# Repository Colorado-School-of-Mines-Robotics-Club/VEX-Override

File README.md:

# VEX Override

This is the codebase for VURC team ORDGR's 26-27 Override season.

## Development environment setup

A nix flake is provided with a `devShell` output providing all the necessary
tools plus some extra. If you have nix installed, you can use that. If you
don't, all the necessary tools are listed below:

1. `rustup`
    - Follow the instructions at https://www.rust-lang.org/tools/install
    - This project requires nightly and has a `rust-toolchain.toml` defining the specific toolchain version.
2. `cargo-v5`
    - Used for building and uploading to the brain
    - Can be installed with cargo: `cargo install cargo-v5`
3. `picotool`
    - Used for uploading code to the Pico microcontroller over BOOTSEL mode
    - If using a probe tool, this isn't strictly necessary
    - Can be downloaded from the official Pico SDK at `https://github.com/raspberrypi/pico-sdk-tools/releases`
    - Example: `picotool load -u -v -x -t elf <executable>`
4. `probe-rs`
    - Used for uploading code and debugging the Pico microcontroller with a probe tool
    - If no probe tool is available, use BOOTSEL mode and `picotool` instead
    - Can be installed with cargo: `cargo install probe-rs`

## Project layout

> [!IMPORTANT]
> Due to limitations in how cargo handles multi-target projects, you
> must actively be in the `brain/` or `pico/` folder to build or upload
> code: run `cd brain` or `cd pico` before using any cargo commands.

| Folder                                     | Description                                                                                                                   |
| ------------------------------------------ | ----------------------------------------------------------------------------------------------------------------------------- |
| [`brain/bots`](./brain/bots)               | Top-level code running on our bots' v5 brains, setting up subsystems and declaring autonomous routes                          |
| [`brain/common`](./brain/common)           | Bot-agnostic v5 brain code such as shared subsystems or display logic                                                         |
| [`brain/coprocessor`](./brain/coprocessor) | Brain-side logic for communicating with the Pico microcontroller                                                              |
| [`pico/`](./pico/)                         | The code running on the Raspberry Pi Pico 2 microcontroller we use on our bots                                                |
| [`rplidar/`](./rplidar)                    | Rust code implementing the prococol for RPLIDAR S & C series devices, may be factored out into a seperate crate at some point |
| [`swerve_c++/`](./swerve_c++)              | Prototype C++ (PROS) code used for initially testing the swerve bot                                                           |
| [`pcb/`](./pcb)                            | The kicad files (schematics, layouts, etc) for the custom PCB connected to our Picos and v5 brains                            |

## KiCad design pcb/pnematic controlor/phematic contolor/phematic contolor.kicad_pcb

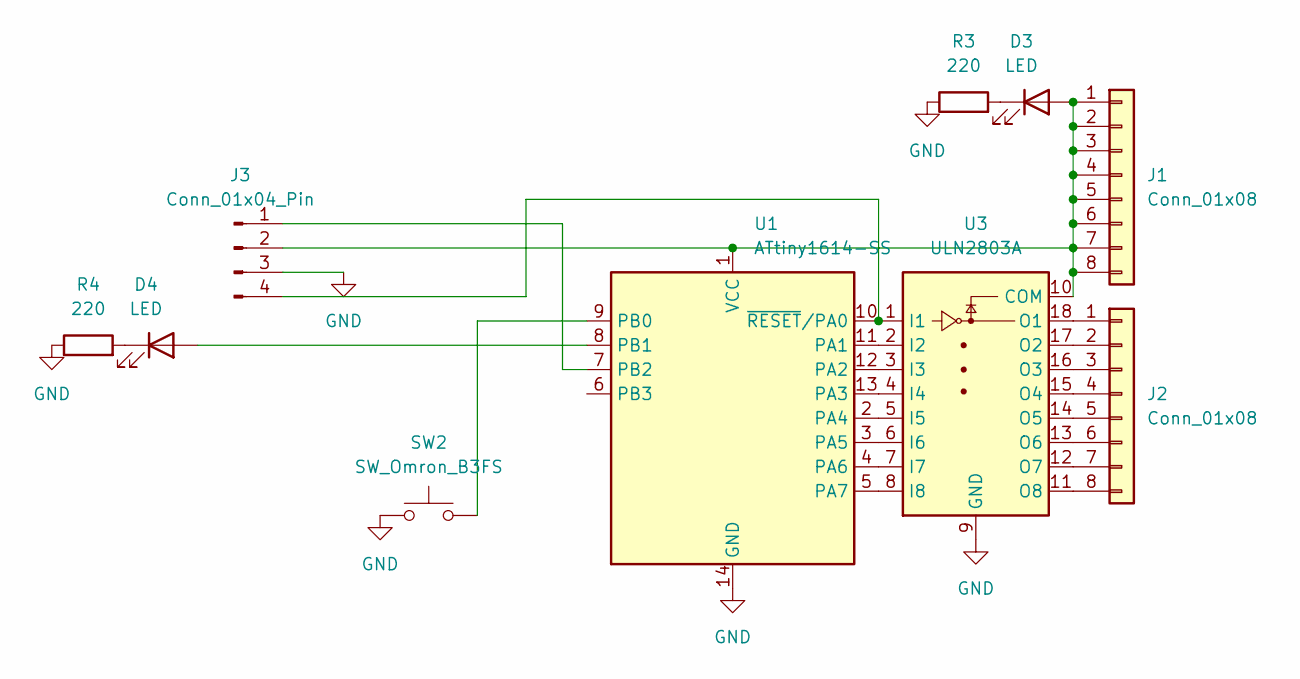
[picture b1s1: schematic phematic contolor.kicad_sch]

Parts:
D3, D4: LED; LED_1206_3216Metric_Pad1.42x1.75mm_HandSolder
J1, J2: Conn_01x08; PinSocket_1x08_P2.54mm_Vertical
J3: Conn_01x04_Pin; PinSocket_1x04_P2.54mm_Vertical
R3, R4: 220; R_1206_3216Metric_Pad1.30x1.75mm_HandSolder
SW2: SW_Omron_B3FS; SW_SPST_Omron_B3FS-101xP
U1: ATtiny1614-SS; SOIC-14_3.9x8.7mm_P1.27mm
U3: ULN2803A; SOIC-18W_7.5x11.6mm_P1.27mm

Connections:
GND: J3.3, R3.1, R4.1, SW2.1, U1.14 (GND), U3.9 (GND)
unnamed: D3.2 (A), J1.1, J1.2, J1.3, J1.4, J1.5, J1.6, J1.7, J1.8, J3.2, U1.1 (VCC), U3.10 (COM)
unnamed: D3.1 (K), R3.2
unnamed: D4.2 (A), U1.8 (PB1)
unnamed: D4.1 (K), R4.2
unnamed: J2.1, U3.18 (O1)
unnamed: J2.2, U3.17 (O2)
unnamed: J2.3, U3.16 (O3)
unnamed: J2.4, U3.15 (O4)
unnamed: J2.5, U3.14 (O5)
unnamed: J2.6, U3.13 (O6)
unnamed: J2.7, U3.12 (O7)
unnamed: J2.8, U3.11 (O8)
unnamed: J3.1, U1.7 (PB2)
unnamed: J3.4, U1.10 (~RESET/PA0), U3.1 (I1)
unnamed: U1.11 (PA1), U3.2 (I2)
unnamed: U1.12 (PA2), U3.3 (I3)
unnamed: U1.13 (PA3), U3.4 (I4)
unnamed: U1.2 (PA4), U3.5 (I5)
unnamed: U1.3 (PA5), U3.6 (I6)
unnamed: U1.4 (PA6), U3.7 (I7)
unnamed: U1.5 (PA7), U3.8 (I8)
unnamed: SW2.2, U1.9 (PB0)

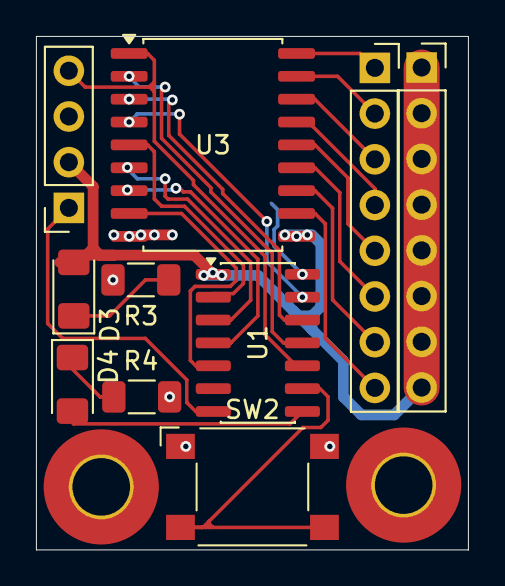
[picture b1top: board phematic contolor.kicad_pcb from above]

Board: 2 copper layers, 24.0 x 28.5 mm, 10 parts (0 on the bottom side), 23 nets.

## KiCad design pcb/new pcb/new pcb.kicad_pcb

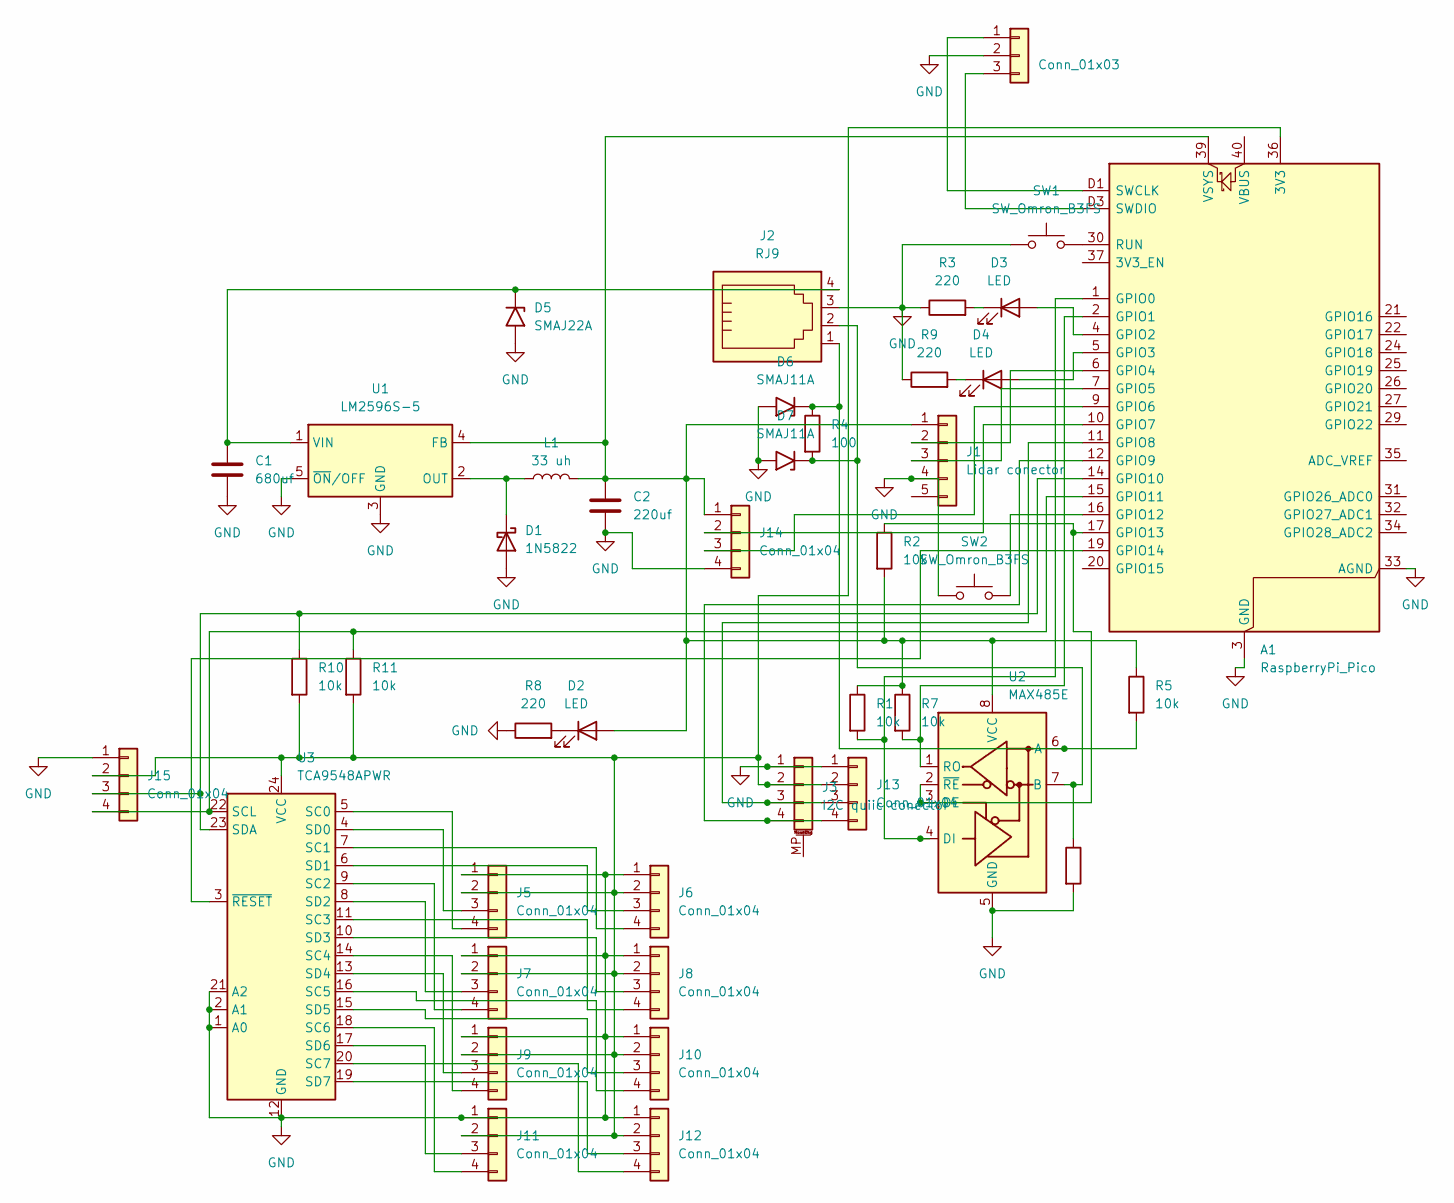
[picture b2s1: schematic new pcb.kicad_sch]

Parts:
A1: RaspberryPi_Pico; RaspberryPi_Pico_SMD_HandSolder
C1: 680uf; C_Radial_D6.3mm_H5.0mm_P2.50mm
C2: 220uf; C_Radial_D6.3mm_H5.0mm_P2.50mm
D1: 1N5822; D_SMC
D2, D3, D4: LED; LED_1206_3216Metric_Pad1.42x1.75mm_HandSolder
D5: SMAJ22A; D_SMA
D6, D7: SMAJ11A; D_SMA
J1: Lidar conector; JST_XH_B5B-XH-A_1x05_P2.50mm_Vertical
J2: RJ9; RJ9_Evercom_5301-440xxx_Horizontal
J3: I2C quiic conector; JST_SH_SM04B-SRSS-TB_1x04-1MP_P1.00mm_Horizontal
J5, J6, J7, J8, J9, J10, J11, J12, J13, J14, J15: Conn_01x04; JST_XH_B4B-XH-A_1x04_P2.50mm_Vertical
L1: 33 uh; L_Bourns_SRR1260
R1, R2, R5, R6, R7, R10, R11: 10k; R_1206_3216Metric_Pad1.30x1.75mm_HandSolder
R3, R8, R9: 220; R_1206_3216Metric_Pad1.30x1.75mm_HandSolder
R4: 100; R_1206_3216Metric_Pad1.30x1.75mm_HandSolder
SW1, SW2: SW_Omron_B3FS; SW_SPST_Omron_B3FS-101xP
U1: LM2596S-5; TO-263-5_TabPin3
U2: MAX485E; SOIC-8_3.9x4.9mm_P1.27mm
U3: TCA9548APWR; TSSOP-24_4.4x7.8mm_P0.65mm
debug1: Conn_01x03; JST_SH_SM03B-SRSS-TB_1x03-1MP_P1.00mm_Horizontal

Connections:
GND: A1.3 (GND), A1.8 (GND), A1.13 (GND), A1.18 (GND), A1.23 (GND), A1.28 (GND), A1.33 (AGND), A1.38 (GND), A1.D2 (GND), C1.2, C2.2, D1.2 (A), D5.2 (A2), D6.2 (A2), D7.2 (A2), J1.4, J2.3, J3.1, J5.1, J6.1, J7.1, J8.1, J9.1, J10.1, J11.1, J12.1, J13.1, J14.4, J15.1, R3.1, R6.2, R8.1, R9.1, SW1.1, SW2.1, U1.3 (GND), U1.5 (~ON/OFF), U2.5 (GND), U3.1 (A0), U3.2 (A1), U3.12 (GND), U3.21 (A2), debug1.2
unnamed: A1.36 (3V3), J3.2, J5.2, J6.2, J7.2, J8.2, J9.2, J10.2, J11.2, J12.2, J13.2, J15.2, R10.2, R11.2, U3.24 (VCC)
unnamed: A1.1 (GPIO0), R1.2, U2.4 (DI)
unnamed: A1.2 (GPIO1), R7.2, U2.1 (RO)
unnamed: A1.4 (GPIO2), D3.2 (A)
unnamed: A1.5 (GPIO3), D4.2 (A)
unnamed: A1.6 (GPIO4), J1.2
unnamed: A1.7 (GPIO5), J1.3
unnamed: A1.9 (GPIO6), J14.3
unnamed: A1.10 (GPIO7), J14.2
unnamed: A1.11 (GPIO8), J3.3, J13.3
unnamed: A1.12 (GPIO9), J3.4, J13.4
unnamed: A1.14 (GPIO10), J15.3, R10.1, U3.23 (SDA)
unnamed: A1.15 (GPIO11), J15.4, R11.1, U3.22 (SCL)
unnamed: A1.16 (GPIO12), SW2.2
unnamed: A1.17 (GPIO13), R2.1, U2.2 (~RE), U2.3 (DE)
unnamed: A1.19 (GPIO14), U3.3 (~RESET)
unnamed: A1.30 (RUN), SW1.2
unnamed: A1.D1 (SWCLK), debug1.1
unnamed: A1.D3 (SWDIO), debug1.3
unnamed: A1.39 (VSYS), C2.1, D2.2 (A), J1.1, J14.1, L1.2, R1.1, R2.2, R5.1, R7.1, U1.4 (FB), U2.8 (VCC)
unnamed: D1.1 (K), L1.1, U1.2 (OUT)
unnamed: D2.1 (K), R8.2
unnamed: D3.1 (K), R3.2
unnamed: D4.1 (K), R9.2
unnamed: C1.1, D5.1 (A1), J2.4, U1.1 (VIN)
unnamed: D6.1 (A1), J2.1, R4.1, R5.2, U2.6 (A)
unnamed: D7.1 (A1), J2.2, R4.2, R6.1, U2.7 (B)
unnamed: J5.3, U3.4 (SD0)
unnamed: J5.4, U3.5 (SC0)
unnamed: J6.3, U3.6 (SD1)
unnamed: J6.4, U3.7 (SC1)
unnamed: J7.3, U3.8 (SD2)
unnamed: J7.4, U3.9 (SC2)
unnamed: J8.3, U3.10 (SD3)
unnamed: J8.4, U3.11 (SC3)
unnamed: J9.3, U3.13 (SD4)
unnamed: J9.4, U3.14 (SC4)
unnamed: J10.3, U3.15 (SD5)
unnamed: J10.4, U3.16 (SC5)
unnamed: J11.3, U3.17 (SD6)
unnamed: J11.4, U3.18 (SC6)
unnamed: J12.3, U3.19 (SD7)
unnamed: J12.4, U3.20 (SC7)

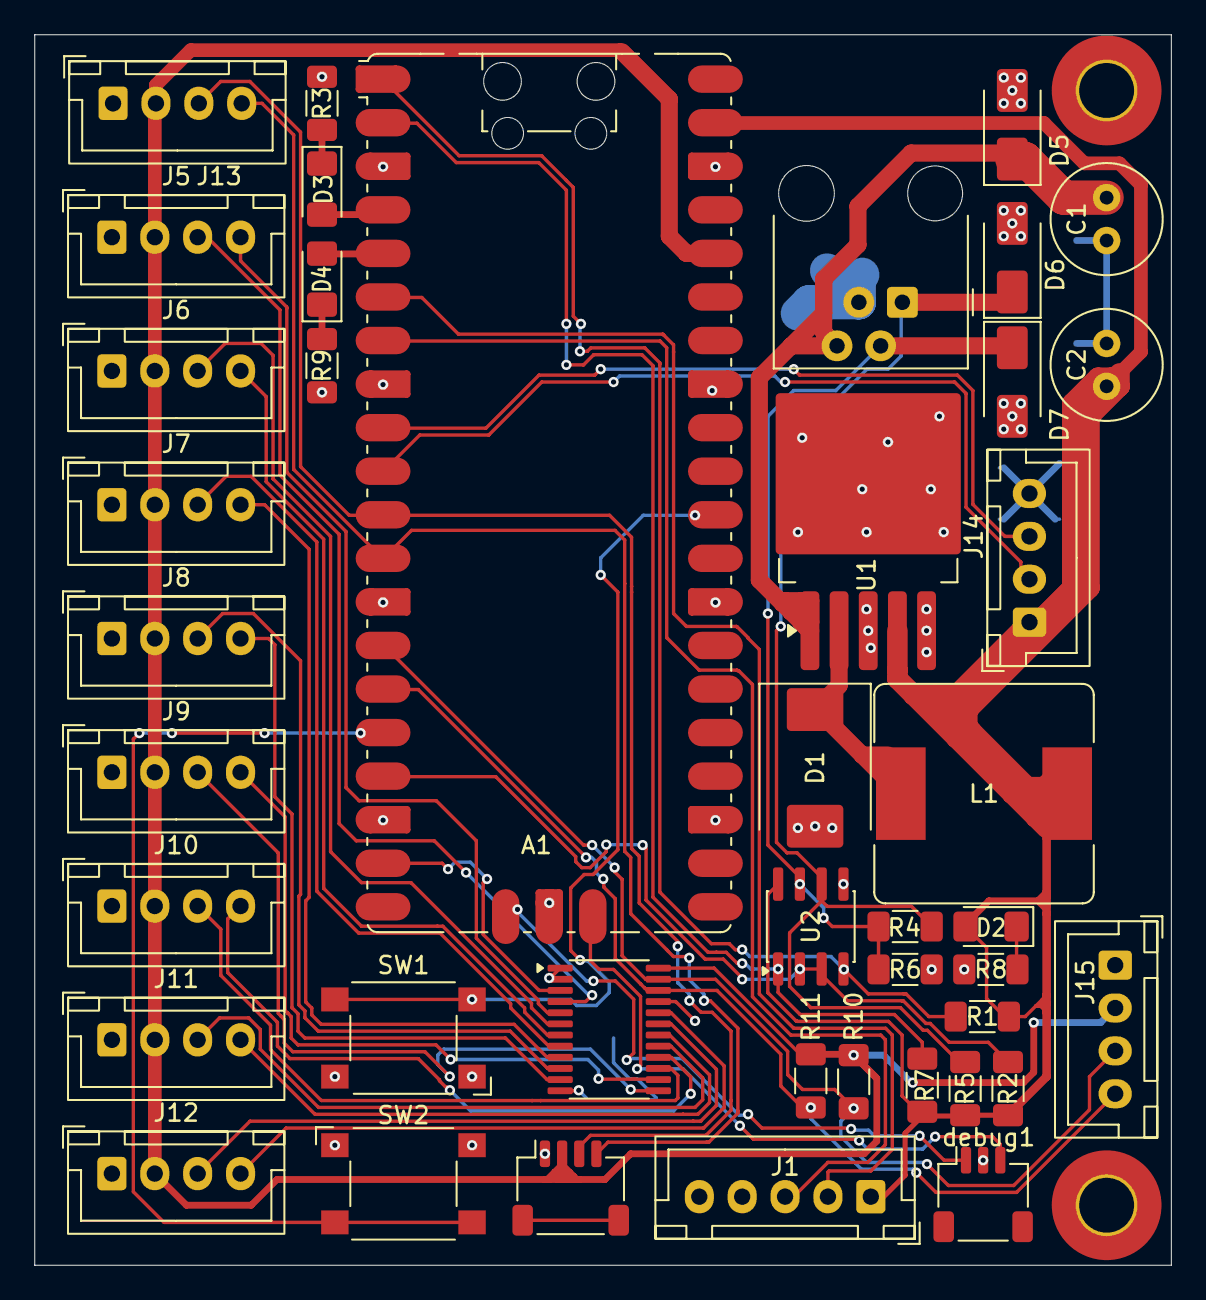
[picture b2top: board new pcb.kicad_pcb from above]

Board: 2 copper layers, 66.3 x 71.8 mm, 42 parts (0 on the bottom side), 44 nets.

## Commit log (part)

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2026-05-03 Init with embassy-rp pico code & last season's brain-side copro code
2026-05-03 Add pcb folder & kicad to flake
2026-05-04 Reorganize to fix cargo config issues, add readme
2026-05-04 added the pcb files
2026-05-04 fix the pcb
2026-05-04 actual fix
2026-05-04 Add warning about being in the correct directory for brain vs. pico code
2026-05-04 Add comments to Cargo.toml
2026-05-04 added reset to gpio14
2026-05-04 pcb production
2026-05-04 origanal swerve code (bad)
2026-05-06 Remake push back's UI in buoyant
2026-05-06 Remove unnecessary extra display instance
2026-05-06 updating encoder values
2026-05-08 refactor vexide code into main display crate, add calibrate button
2026-05-16 Update deps, derive Debug for display state, cleanup
